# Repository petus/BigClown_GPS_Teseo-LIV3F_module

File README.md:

# BigClown_GPS_Teseo-LIV3F_module
GPS module for BigClown platform with Teseo-LIV3F by STMicroelectronics

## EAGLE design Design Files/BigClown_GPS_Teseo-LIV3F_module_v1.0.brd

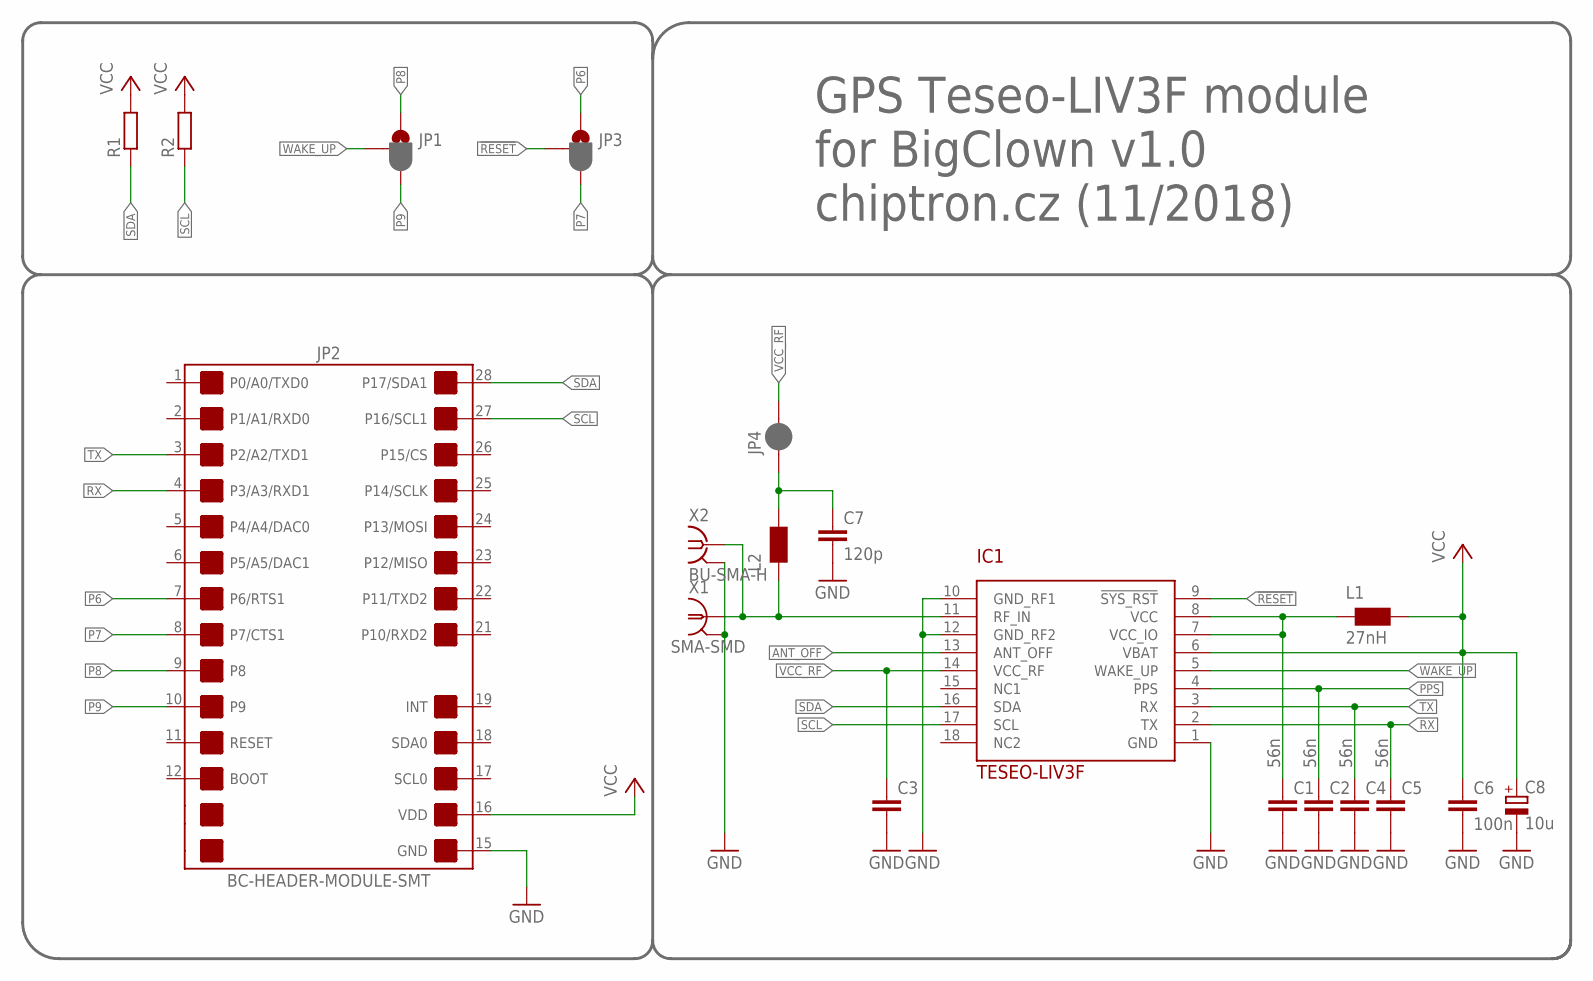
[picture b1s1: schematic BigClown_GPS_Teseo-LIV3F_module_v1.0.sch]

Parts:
C1, C2, C4, C5: 56n; C0805
C3: C-EUC0805; C0805
C6: 100n; C0805
C7: 120p; C0805
C8: 10u; SMC_B
IC1: TESEO-LIV3F
JP1, JP3: JUMPER-SMT_3_1-NC_PASTE_SILK; SMT-JUMPER_3_1-NC_PASTE_SILK
JP2: BC-HEADER-MODULE-SMT
JP4: JUMPER-SMT_2_NC_PASTE_SILK; SMT-JUMPER_2_NC_PASTE_SILK
L1: 27nH; 0805
L2: 33nF; 0805
R1, R2: R-EU_M0805; M0805
X1: SMA-SMD
X2: BU-SMA-H

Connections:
!RESET: IC1.9 (!SYS_RST), JP3.2
ANT_OFF: IC1.13 (ANT_OFF)
GND: C1.2, C2.2, C3.2, C4.2, C5.2, C6.2, C7.2, C8.-, IC1.1 (GND), IC1.10 (GND_RF1), IC1.12 (GND_RF2), JP2.15 (GND), X1.2@1 (2), X1.2@2 (2), X1.2@3 (2), X1.2@4 (2), X1.2@5 (2), X1.2@6 (2), X2.2, X2.3 (2), X2.4 (2), X2.5 (2)
unnamed: C1.1, IC1.7 (VCC_IO), IC1.8 (VCC), L1.1
unnamed: IC1.11 (RF_IN), L2.1, X1.1, X2.1
unnamed: C7.1, JP4.1, L2.2
P6: JP2.7 (P6/RTS1), JP3.1
P7: JP2.8 (P7/CTS1), JP3.3
P8: JP1.1, JP2.9 (P8)
P9: JP1.3, JP2.10 (P9)
PPS: C2.1, IC1.4 (PPS)
RX: C5.1, IC1.2 (TX), JP2.4 (P3/A3/RXD1)
SCL: IC1.17 (SCL), JP2.27 (P16/SCL1), R2.1
SDA: IC1.16 (SDA), JP2.28 (P17/SDA1), R1.1
TX: C4.1, IC1.3 (RX), JP2.3 (P2/A2/TXD1)
VCC: C6.1, C8.+, IC1.6 (VBAT), JP2.16 (VDD), L1.2, R1.2, R2.2
VCC_RF: C3.1, IC1.14 (VCC_RF), JP4.2
WAKE_UP: IC1.5 (WAKE_UP), JP1.2

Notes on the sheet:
GPS Teseo-LIV3F module for BigClown v1.0 chiptron.cz (11/2018)

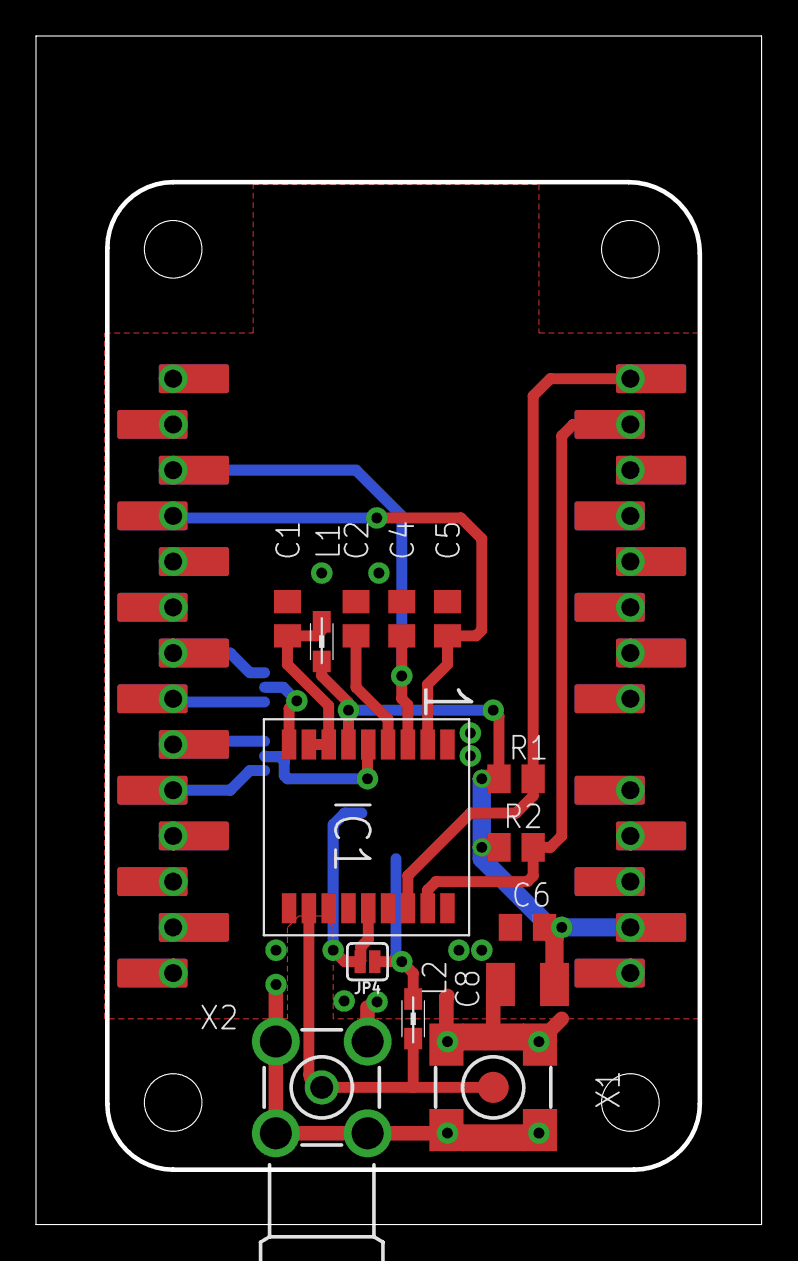
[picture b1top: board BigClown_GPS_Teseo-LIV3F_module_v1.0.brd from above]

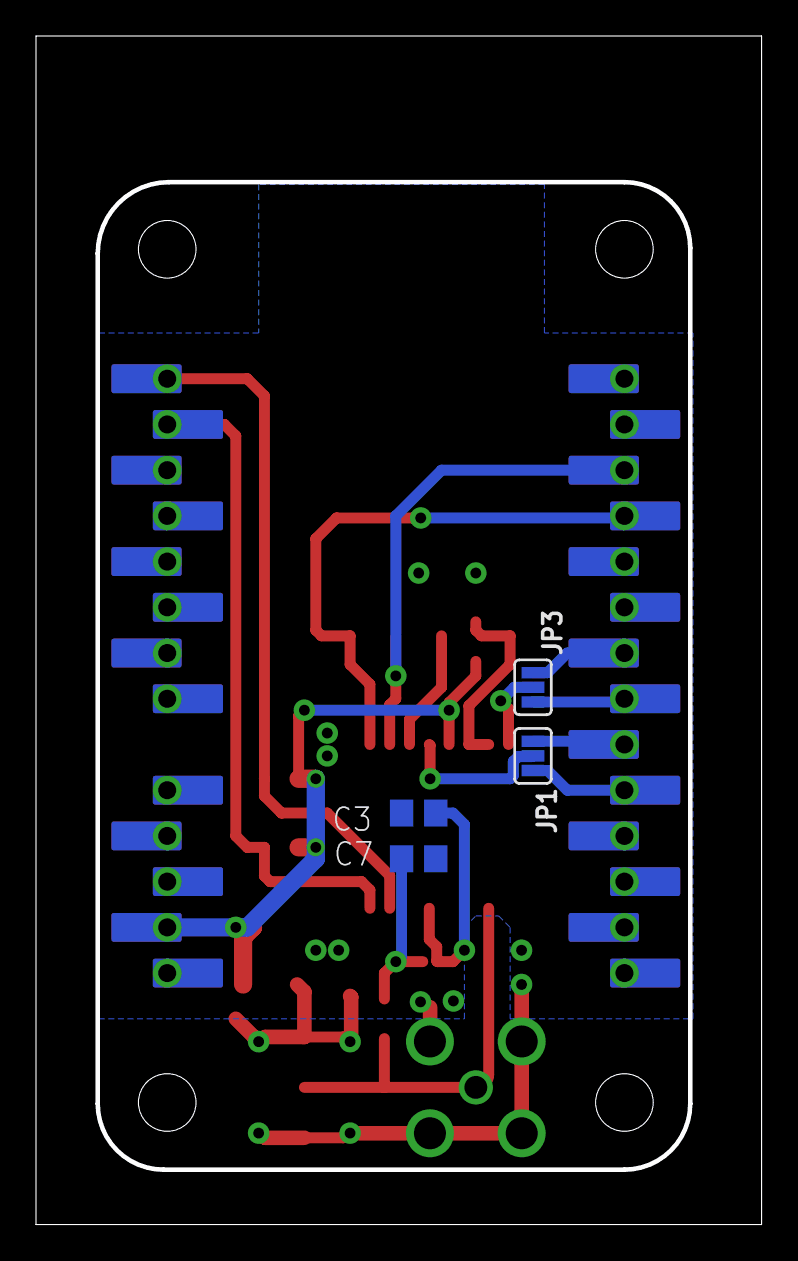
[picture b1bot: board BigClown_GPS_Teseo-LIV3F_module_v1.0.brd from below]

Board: 2 copper layers, 40.1 x 65.8 mm, 19 parts (4 on the bottom side), 17 nets.

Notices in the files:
parts and their libraries:
wuerth-elektronik: Copyright: Würth Elektronik eiSos
SparkFun-Jumpers: Licensing: Creative Commons ShareAlike 4.0 International - https://creativecommons.org/licenses/by-sa/4.0
